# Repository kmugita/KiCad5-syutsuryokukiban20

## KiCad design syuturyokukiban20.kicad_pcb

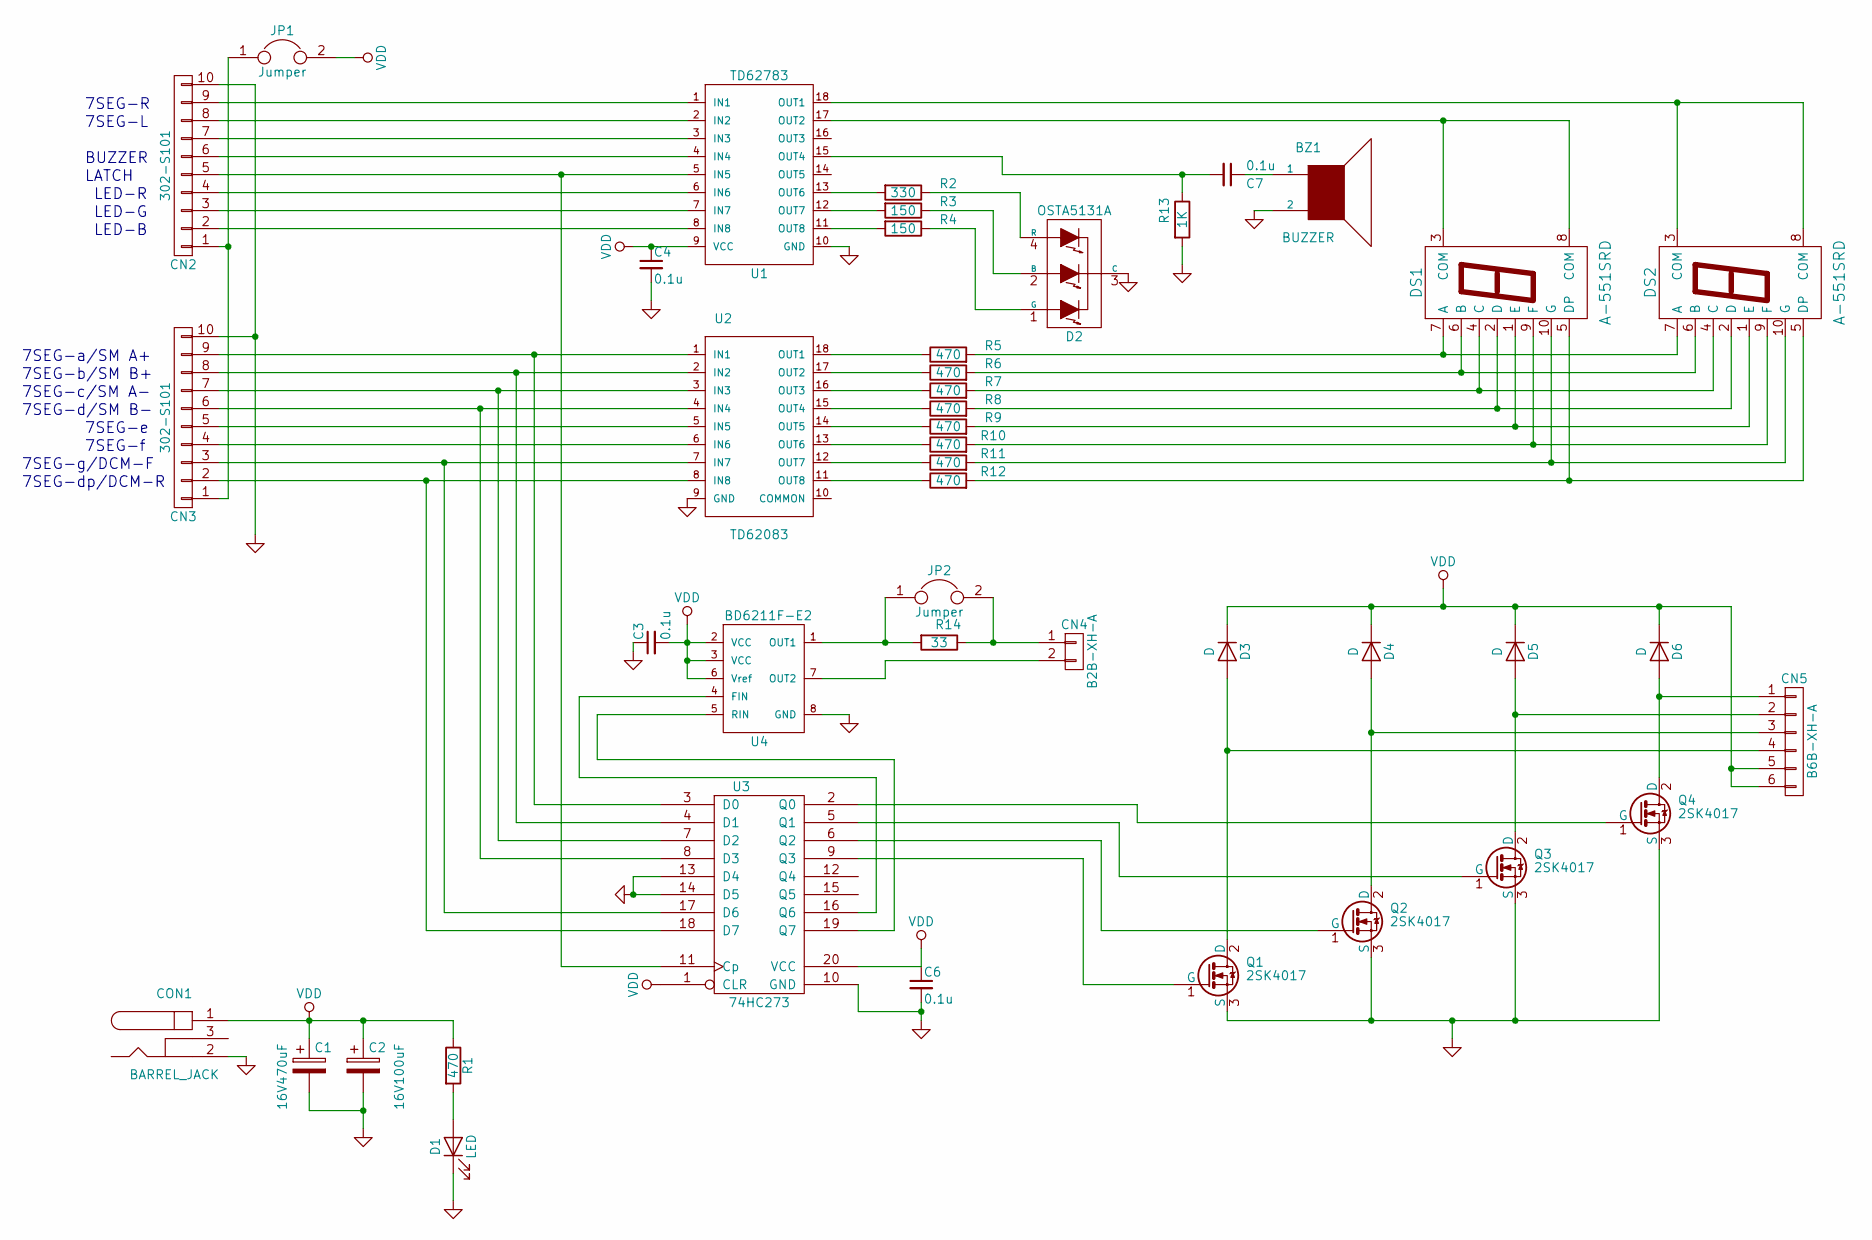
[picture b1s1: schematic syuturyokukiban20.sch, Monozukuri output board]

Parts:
BZ1: BUZZER; Buzzer_12x6.9_Pitch5
C1: 16V470uF; C_Radial_D8_L11.5_P3.5
C2: 16V100uF; C_Radial_D6.3_L11.2_P2.5
C3, C4, C6, C7: 0.1u; C_Rect_L4_W2.5_P2.5
CN2, CN3: 302-S101; IDC_Header_Straight_10pins
CN4: B2B-XH-A; JST_XH_B02B-XH-A_02x2.50mm_Straight
CN5: B6B-XH-A; JST_XH_B06B-XH-A_06x2.50mm_Straight
CON1: BARREL_JACK
D1: LED; LED-5MM
D2: OSTA5131A; LED-OSTA5131A-R_PG_B
D3, D4, D5, D6: D; Diode_DO-35_HOLE09_Horizontal_RM10
DS1, DS2: A-551SRD; 7SegmentLED_A-551SRD-A
JP1, JP2: Jumper; Pin_Header_Straight_1x02
Q1, Q2, Q3, Q4: 2SK4017; SOT126_SOT32_Housing_Vertical_Hole08
R1, R5, R6, R7, R8, R9, R10, R11, R12: 470; Resistor_Horizontal_RM10mm
R2: 330; Resistor_Horizontal_RM10mm
R3, R4: 150; Resistor_Horizontal_RM10mm
R13: 1K; Resistor_Horizontal_RM10mm
R14: 33; Resistor_Horizontal_RM20mm
U1: TD62783; DIP-18_W7.62mm
U2: TD62083; DIP-18_W7.62mm
U3: 74HC273; DIP-20_W7.62mm
U4: BD6211F-E2; SOIC-8_3.9x4.9mm_Pitch1.27mm

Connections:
GND: BZ1.2, C1.2, C2.2, C3.1, C4.2, C6.2, CN2.10, CN3.10, CON1.2, D1.1 (K), D2.3 (C), Q1.3 (S), Q2.3 (S), Q3.3 (S), Q4.3 (S), R13.2, U1.10 (GND), U2.9 (GND), U3.10 (GND), U3.13 (D4), U3.14 (D5), U4.8 (GND)
unnamed: BZ1.1, C7.1
unnamed: C7.2, R13.1, U1.15 (OUT4)
unnamed: CN2.1, CN3.1, JP1.1
unnamed: CN2.2, U1.8 (IN8)
unnamed: CN2.3, U1.7 (IN7)
unnamed: CN2.4, U1.6 (IN6)
unnamed: CN2.5, U1.5 (IN5), U3.11 (Cp)
unnamed: CN2.6, U1.4 (IN4)
unnamed: CN2.7, U1.3 (IN3)
unnamed: CN2.8, U1.2 (IN2)
unnamed: CN2.9, U1.1 (IN1)
unnamed: CN3.2, U2.8 (IN8), U3.18 (D7)
unnamed: CN3.3, U2.7 (IN7), U3.17 (D6)
unnamed: CN3.4, U2.6 (IN6)
unnamed: CN3.5, U2.5 (IN5)
unnamed: CN3.6, U2.4 (IN4), U3.8 (D3)
unnamed: CN3.7, U2.3 (IN3), U3.7 (D2)
unnamed: CN3.8, U2.2 (IN2), U3.4 (D1)
unnamed: CN3.9, U2.1 (IN1), U3.3 (D0)
unnamed: CN4.1, JP2.2, R14.1
unnamed: CN4.2, U4.7 (OUT2)
unnamed: CN5.1, D6.2 (A), Q4.2 (D)
unnamed: CN5.2, D5.2 (A), Q3.2 (D)
unnamed: CN5.3, D4.2 (A), Q2.2 (D)
unnamed: CN5.4, D3.2 (A), Q1.2 (D)
unnamed: D1.2 (A), R1.2
unnamed: D2.1 (G), R4.1
unnamed: D2.2 (B), R3.1
unnamed: D2.4 (R), R2.1
unnamed: DS1.1 (E), DS2.1 (E), R9.2
unnamed: DS1.2 (D), DS2.2 (D), R8.2
unnamed: DS1.3 (COM), DS1.8 (COM), U1.17 (OUT2)
unnamed: DS1.4 (C), DS2.4 (C), R7.2
unnamed: DS1.5 (DP), DS2.5 (DP), R12.2
unnamed: DS1.6 (B), DS2.6 (B), R6.2
unnamed: DS1.7 (A), DS2.7 (A), R5.2
unnamed: DS1.9 (F), DS2.9 (F), R10.2
unnamed: DS1.10 (G), DS2.10 (G), R11.2
unnamed: DS2.3 (COM), DS2.8 (COM), U1.18 (OUT1)
unnamed: JP2.1, R14.2, U4.1 (OUT1)
unnamed: Q1.1 (G), U3.9 (Q3)
unnamed: Q2.1 (G), U3.6 (Q2)
unnamed: Q3.1 (G), U3.5 (Q1)
unnamed: Q4.1 (G), U3.2 (Q0)
unnamed: R2.2, U1.13 (OUT6)
unnamed: R3.2, U1.12 (OUT7)
unnamed: R4.2, U1.11 (OUT8)
unnamed: R5.1, U2.18 (OUT1)
unnamed: R6.1, U2.17 (OUT2)
unnamed: R7.1, U2.16 (OUT3)
unnamed: R8.1, U2.15 (OUT4)
unnamed: R9.1, U2.14 (OUT5)
unnamed: R10.1, U2.13 (OUT6)
unnamed: R11.1, U2.12 (OUT7)
unnamed: R12.1, U2.11 (OUT8)
unnamed: U3.16 (Q6), U4.4 (FIN)
unnamed: U3.19 (Q7), U4.5 (RIN)
VDD: C1.1, C2.1, C3.2, C4.1, C6.1, CN5.5, CN5.6, CON1.1, D3.1 (K), D4.1 (K), D5.1 (K), D6.1 (K), JP1.2, R1.1, U1.9 (VCC), U3.1 (CLR), U3.20 (VCC), U4.2 (VCC), U4.3 (VCC), U4.6 (Vref)

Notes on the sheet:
LED-B
LED-G
LED-R
LATCH
BUZZER
7SEG-L
7SEG-R
7SEG-dp/DCM-R
7SEG-g/DCM-F
7SEG-f
7SEG-e
7SEG-c/SM A-
7SEG-d/SM B-
7SEG-b/SM B+
7SEG-a/SM A+

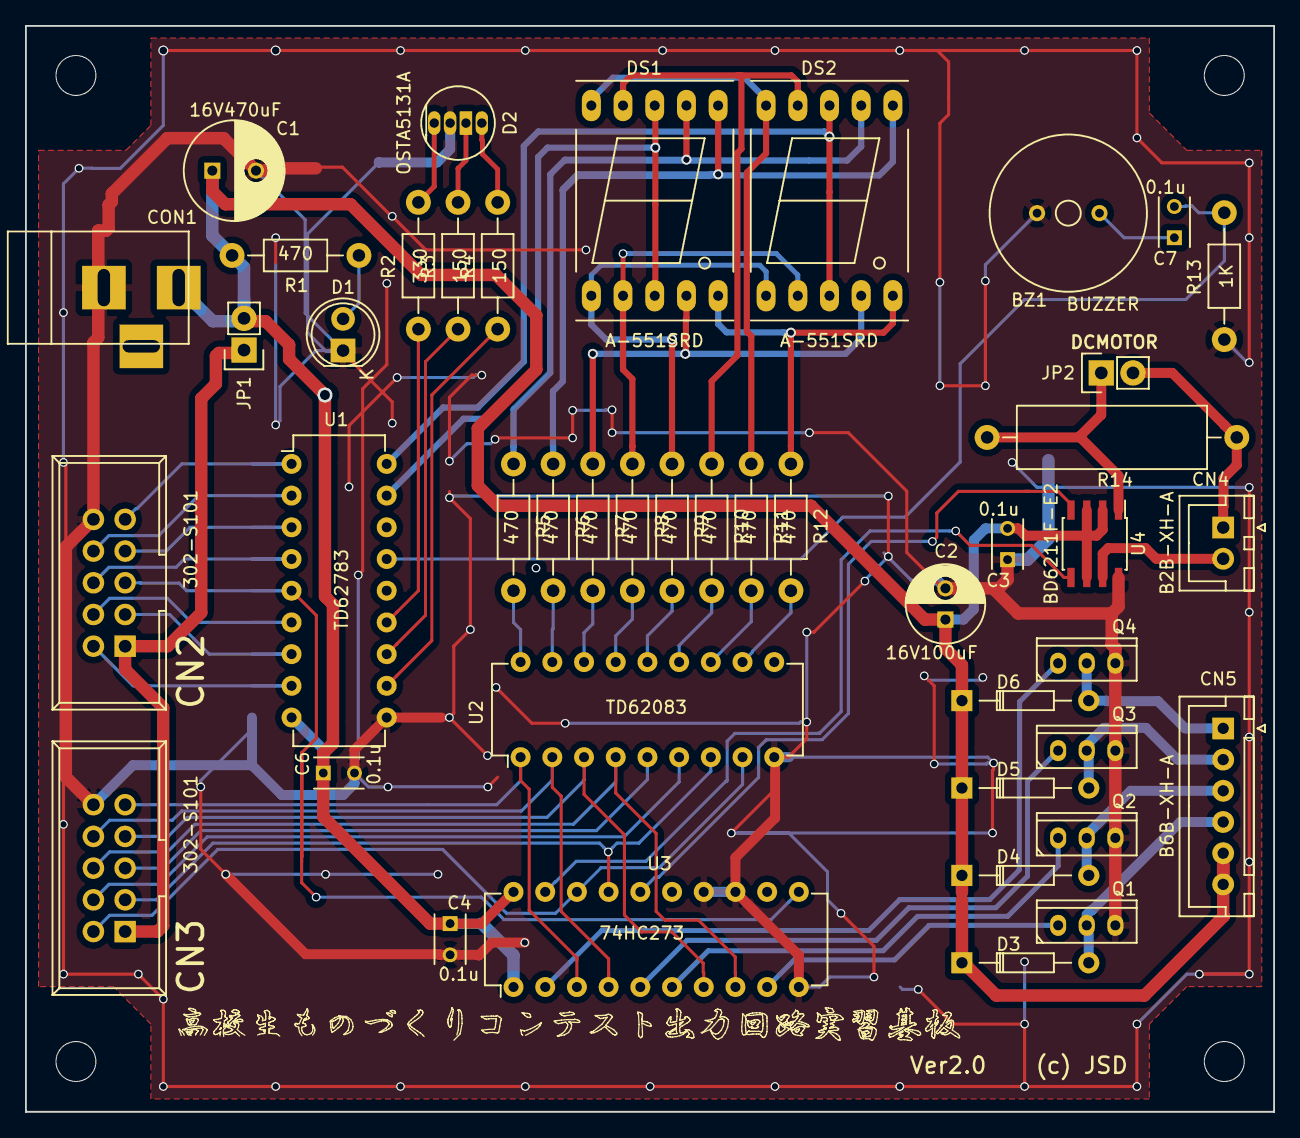
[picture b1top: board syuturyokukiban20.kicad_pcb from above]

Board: 2 copper layers, 100.0 x 87.0 mm, 44 parts (0 on the bottom side), 59 nets.

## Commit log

2019-04-29 monozukuri syuturyokukiban v2.0
